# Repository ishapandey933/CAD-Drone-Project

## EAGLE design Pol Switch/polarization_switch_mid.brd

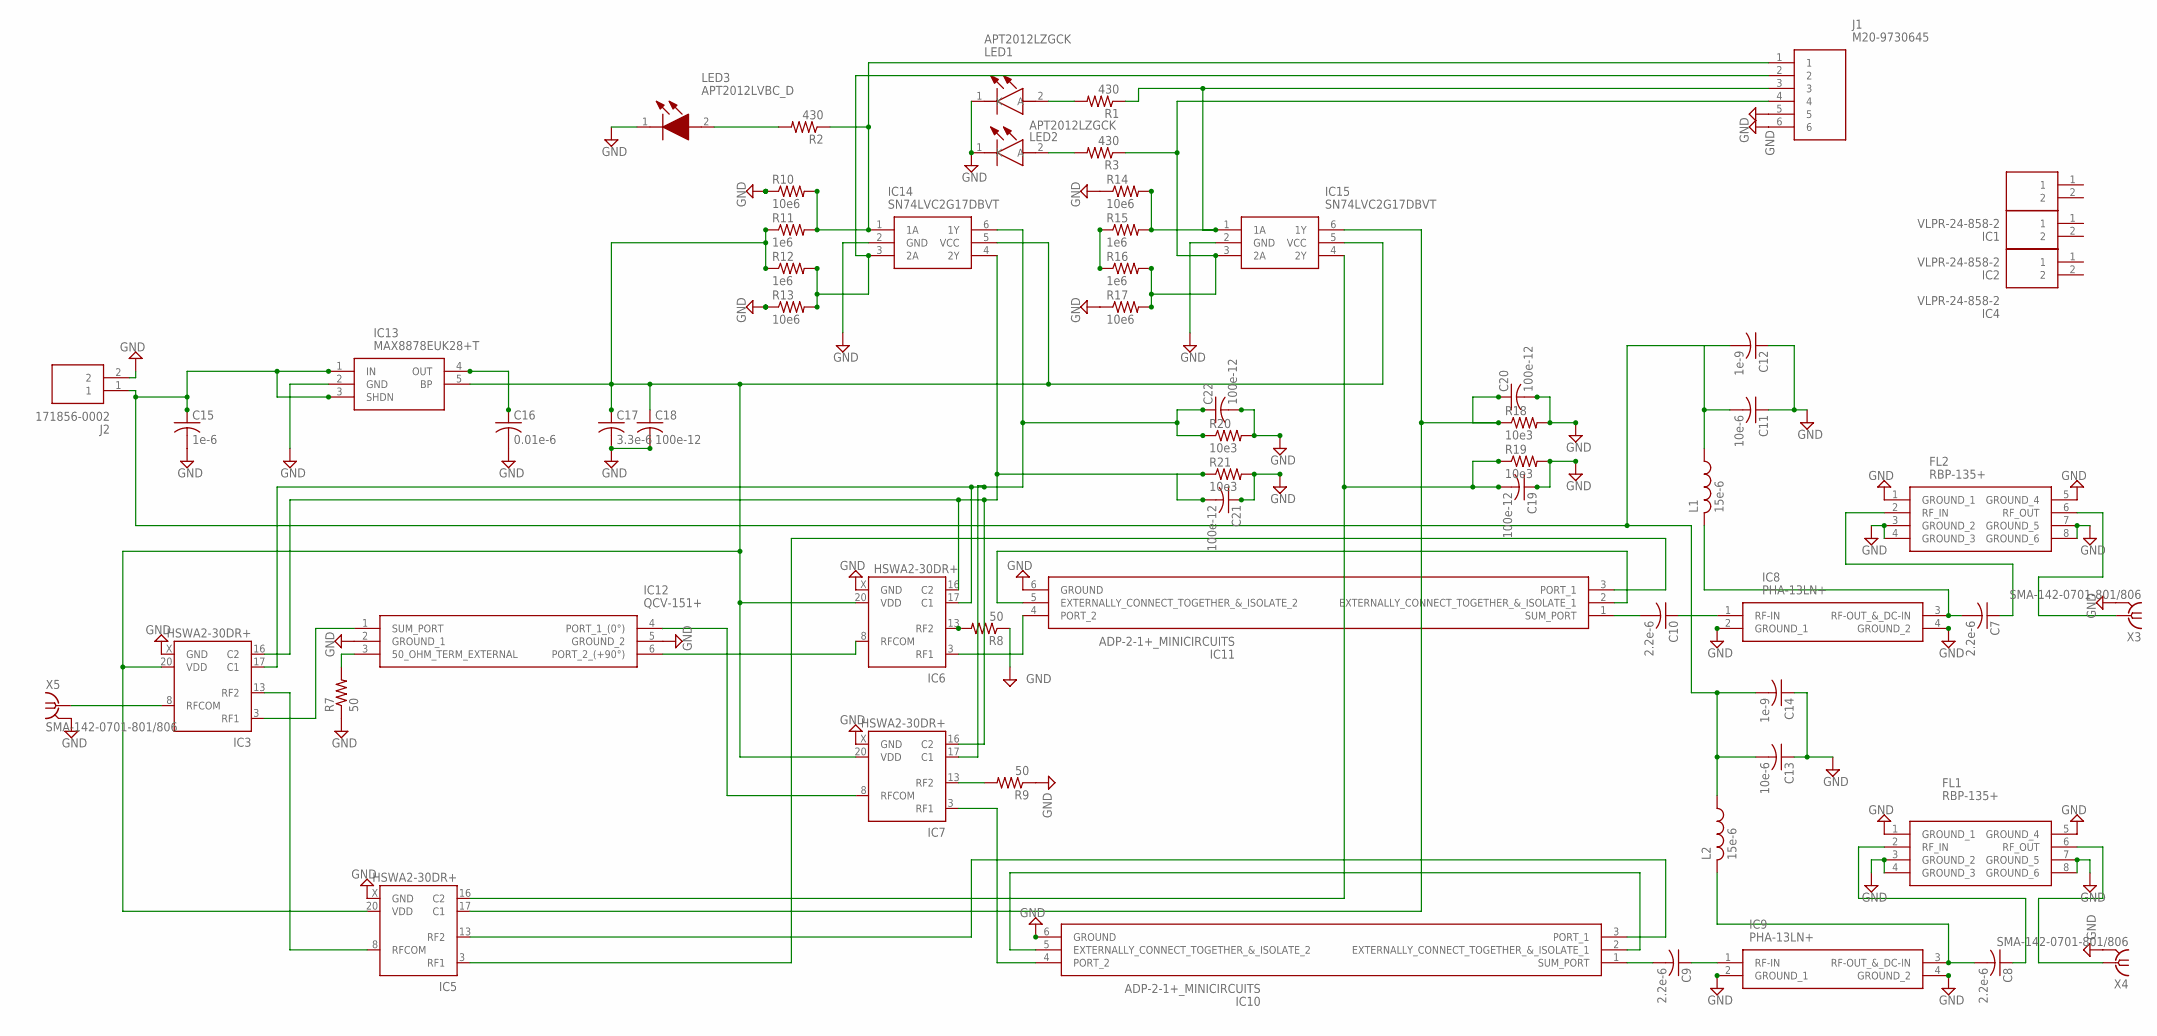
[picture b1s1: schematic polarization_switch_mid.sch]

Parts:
C7, C8, C9, C10: 2.2e-6; C0603
C11, C13: 10e-6; C0603
C12, C14: 1e-9; C0603
C15: 1e-6; C0603
C16: 0.01e-6; C0603
C17: 3.3e-6; C0603
C18, C19, C20, C21, C22: 100e-12; C0603
FL1, FL2: RBP-135+; RBP135
IC1, IC2, IC4: VLPR-24-858-2; VLPR248582
IC3, IC5, IC6, IC7: HSWA2-30DR+; DG983-1
IC8, IC9: PHA-13LN+; PHA13LN
IC10, IC11: ADP-2-1+_MINICIRCUITS; SOTFL254P691X411-6N
IC12: QCV-151+; QCV151
IC13: MAX8878EUK28+T; SOT95P280X145-5N
IC14, IC15: SN74LVC2G17DBVT; SOT95P280X145-6N
J1: M20-9730645; HDRV6W66P0X254_1X6_1524X254X96
J2: 171856-0002; SHDR2W90P0X254_1X2_493X635X106
L1, L2: 15e-6; L3225M
LED1, LED2: APT2012LZGCK; LEDC2012X85N
LED3: APT2012LVBC_D; LEDC2012X85N
R1, R2, R3: 430; R0603
R7, R8, R9: 50; R0603
R10, R13, R14, R17: 10e6; R0603
R11, R12, R15, R16: 1e6; R0603
R18, R19, R20, R21: 10e3; R0603
X3, X4, X5: SMA-142-0701-801/806; J502-ND-142-0701-801/806

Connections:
GND: C11.1, C12.1, C13.1, C14.1, C15.2, C16.2, C17.2, C18.2, C19.1, C20.2, C21.1, C22.2, FL1.1 (GROUND_1), FL1.3 (GROUND_2), FL1.4 (GROUND_3), FL1.5 (GROUND_4), FL1.7 (GROUND_5), FL1.8 (GROUND_6), FL2.1 (GROUND_1), FL2.3 (GROUND_2), FL2.4 (GROUND_3), FL2.5 (GROUND_4), FL2.7 (GROUND_5), FL2.8 (GROUND_6), IC3.1 (GND), IC3.2 (GND), IC3.4 (GND), IC3.5 (GND), IC3.6 (GND), IC3.7 (GND), IC3.9 (GND), IC3.10 (GND), IC3.11 (GND), IC3.12 (GND), IC3.14 (GND), IC3.15 (GND), IC3.18 (GND), IC3.19 (GND), IC3.X (GND), IC5.1 (GND), IC5.2 (GND), IC5.4 (GND), IC5.5 (GND), IC5.6 (GND), IC5.7 (GND), IC5.9 (GND), IC5.10 (GND), IC5.11 (GND), IC5.12 (GND), IC5.14 (GND), IC5.15 (GND), IC5.18 (GND), IC5.19 (GND), IC5.X (GND), IC6.1 (GND), IC6.2 (GND), IC6.4 (GND), IC6.5 (GND), IC6.6 (GND), IC6.7 (GND), IC6.9 (GND), IC6.10 (GND), IC6.11 (GND), IC6.12 (GND), IC6.14 (GND), IC6.15 (GND), IC6.18 (GND), IC6.19 (GND), IC6.X (GND), IC7.1 (GND), IC7.2 (GND), IC7.4 (GND), IC7.5 (GND), IC7.6 (GND), IC7.7 (GND), IC7.9 (GND), IC7.10 (GND), IC7.11 (GND), IC7.12 (GND), IC7.14 (GND), IC7.15 (GND), IC7.18 (GND), IC7.19 (GND), IC7.X (GND), IC8.2 (GROUND_1), IC8.4 (GROUND_2), IC9.2 (GROUND_1), IC9.4 (GROUND_2), IC10.6 (GROUND), IC11.6 (GROUND), IC12.2 (GROUND_1), IC12.5 (GROUND_2), IC13.2 (GND), IC14.2 (GND), IC15.2 (GND), J1.5, J1.6, J2.2, LED1.1 (K), LED2.1 (K), LED3.1 (K), R7.1, R8.1, R9.1, R10.1, R13.1, R14.1, R17.1, R18.2, R19.2, R20.2, R21.2, X3.G@1 (2), X3.G@2 (2), X3.G@3 (2), X3.G@4 (2), X4.G@1 (2), X4.G@2 (2), X4.G@3 (2), X4.G@4 (2), X5.G@1 (2), X5.G@2 (2), X5.G@3 (2), X5.G@4 (2)
unnamed: LED2.2 (A), R3.2
unnamed: LED1.2 (A), R1.2
unnamed: LED3.2 (A), R2.2
unnamed: IC5.13 (RF2), IC10.3 (PORT_1)
unnamed: IC3.8 (RFCOM), X5.1
unnamed: C10.2, IC11.1 (SUM_PORT)
unnamed: IC7.3 (RF1), IC10.4 (PORT_2)
unnamed: C20.1, IC5.17 (C1), IC15.6 (1Y), R18.1
unnamed: IC7.8 (RFCOM), IC12.4 (PORT_1_(0°))
unnamed: C10.1, IC8.1 (RF-IN)
unnamed: IC3.3 (RF1), IC12.1 (SUM_PORT)
unnamed: IC3.13 (RF2), IC5.8 (RFCOM)
unnamed: IC6.8 (RFCOM), IC12.6 (PORT_2_(+90°))
unnamed: IC6.3 (RF1), IC11.4 (PORT_2)
unnamed: IC6.13 (RF2), R8.2
unnamed: C7.2, IC8.3 (RF-OUT_&_DC-IN), L1.2
unnamed: C9.2, IC10.1 (SUM_PORT)
unnamed: IC11.2 (EXTERNALLY_CONNECT_TOGETHER_&_ISOLATE_1), IC11.5 (EXTERNALLY_CONNECT_TOGETHER_&_ISOLATE_2)
unnamed: IC5.3 (RF1), IC11.3 (PORT_1)
unnamed: IC10.2 (EXTERNALLY_CONNECT_TOGETHER_&_ISOLATE_1), IC10.5 (EXTERNALLY_CONNECT_TOGETHER_&_ISOLATE_2)
unnamed: C9.1, IC9.1 (RF-IN)
unnamed: C8.2, IC9.3 (RF-OUT_&_DC-IN), L2.2
unnamed: C7.1, FL2.2 (RF_IN)
unnamed: FL2.6 (RF_OUT), X3.1
unnamed: C8.1, FL1.2 (RF_IN)
unnamed: FL1.6 (RF_OUT), X4.1
unnamed: IC12.3 (50_OHM_TERM_EXTERNAL), R7.2
unnamed: IC7.13 (RF2), R9.2
unnamed: C11.2, C12.2, C13.2, C14.2, C15.1, IC13.1 (IN), IC13.3 (SHDN), J2.1, L1.1, L2.1
unnamed: IC14.1 (1A), J1.1, R2.1, R10.2, R11.2
unnamed: C19.2, IC5.16 (C2), IC15.4 (2Y), R19.1
unnamed: C17.1, C18.1, IC3.20 (VDD), IC5.20 (VDD), IC6.20 (VDD), IC7.20 (VDD), IC13.5 (BP), IC14.5 (VCC), IC15.5 (VCC), R11.1, R12.1
unnamed: C16.1, IC13.4 (OUT)
unnamed: C22.1, IC3.17 (C1), IC6.17 (C1), IC7.17 (C1), IC14.6 (1Y), R20.1
unnamed: IC14.3 (2A), J1.2, R12.2, R13.2
unnamed: IC15.1 (1A), J1.3, R1.1, R14.2, R15.2
unnamed: IC15.3 (2A), J1.4, R3.1, R16.2, R17.2
unnamed: C21.2, IC3.16 (C2), IC6.16 (C2), IC7.16 (C2), IC14.4 (2Y), R21.1
unnamed: R15.1, R16.1

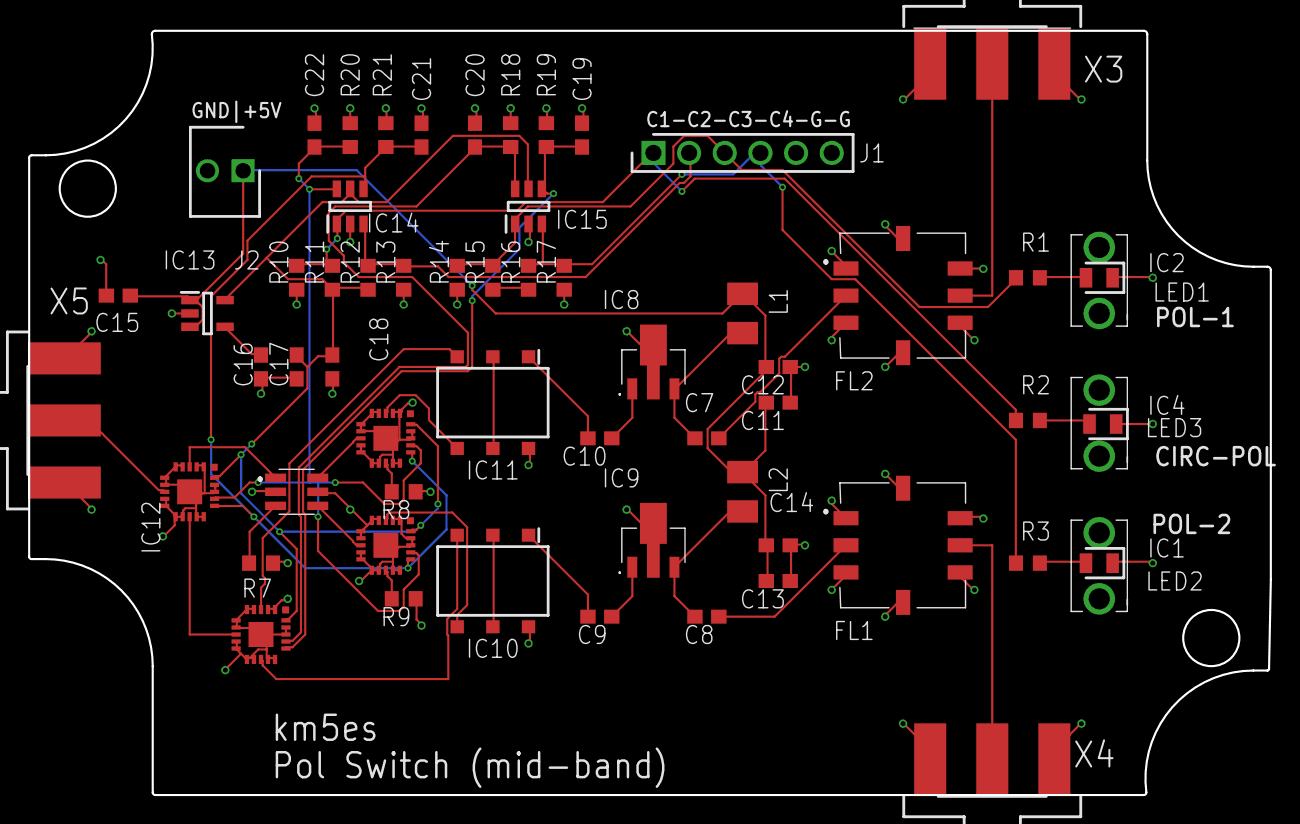
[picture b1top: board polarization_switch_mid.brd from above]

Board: 2 copper layers, 88.4 x 54.4 mm, 61 parts (0 on the bottom side), 40 nets.

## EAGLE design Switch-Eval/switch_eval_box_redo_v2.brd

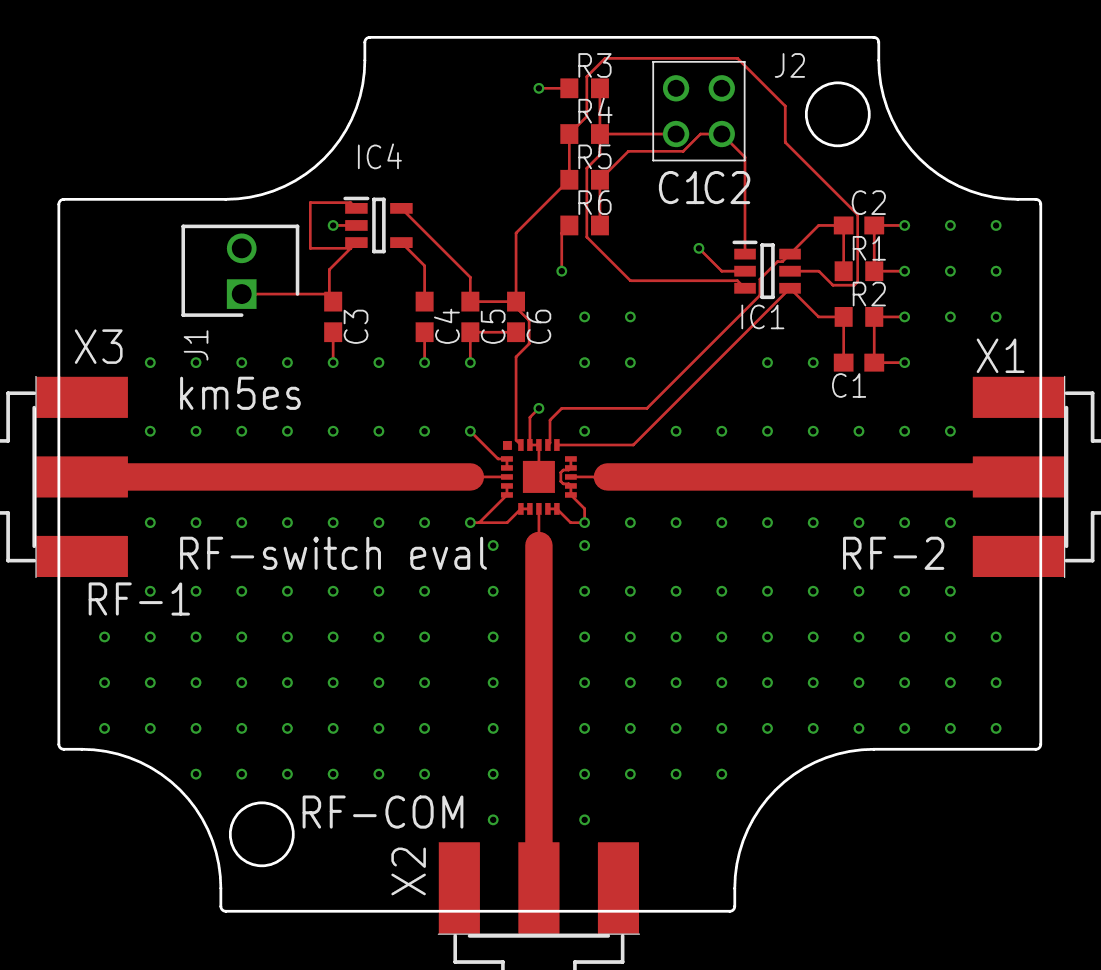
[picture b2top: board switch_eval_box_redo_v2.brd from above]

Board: 2 copper layers, 57.2 x 49.8 mm, 20 parts (0 on the bottom side), 11 nets.

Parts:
C1, C2, C6: 100e-12; C0603
C3: 1e-6; C0603
C4: 0.01e-6; C0603
C5: 3.3e-6; C0603
IC1: SN74LVC2G17DBVT; SOT95P280X145-6N
IC2: HSWA2-30DR+; DG983-1
IC4: MAX8878EUK28+T; SOT95P280X145-5N
J1: 171856-0002; SHDR2W90P0X254_1X2_493X635X106
J2: M20-7830246; M207830246
R1, R2: 10e3; R0603
R3, R6: 10e6; R0603
R4, R5: 1e6; R0603
X1, X2, X3: SMA-142-0701-801/806; J502-ND-142-0701-801/806

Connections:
GND: C1.1, C2.2, C3.2, C4.2, C5.2, C6.2, IC1.2, IC2.1, IC2.2, IC2.4, IC2.5, IC2.6, IC2.7, IC2.9, IC2.10, IC2.11, IC2.12, IC2.14, IC2.15, IC2.18, IC2.19, IC2.X, IC4.2, J1.2, J2.1, J2.2, R1.2, R2.2, R3.1, R6.1, X1.G@1, X1.G@2, X1.G@3, X1.G@4, X2.G@1, X2.G@2, X2.G@3, X2.G@4, X3.G@1, X3.G@2, X3.G@3, X3.G@4
unnamed: IC1.3, J2.3, R3.2, R4.2
unnamed: C3.1, IC4.1, IC4.3, J1.1
unnamed: C4.1, IC4.4
unnamed: IC1.1, J2.4, R5.2, R6.2
unnamed: C5.1, C6.1, IC1.5, IC2.20, IC4.5, R4.1, R5.1
unnamed: IC2.3, X3.1
unnamed: C2.1, IC1.6, IC2.17, R1.1
unnamed: IC2.13, X1.1
unnamed: C1.2, IC1.4, IC2.16, R2.1
unnamed: IC2.8, X2.1
